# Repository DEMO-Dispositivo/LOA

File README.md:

# LOA
Robots for Lucifer's Ensemble LOA project.
Playing 3 drums made using Lavacolhos techniques inspired by the Arada drums and other percussions.
The boards are Arduino-based and can receive MIDI through DIN cable or play via SD Card.

## BOARDS

### Legba 
- Arduino MEGA
- 3 servos (5V)
- 7 solenoids (12V)
- 2 motors (5V or 12V)

### Damballah
- Arduino UNO
- 1 servo (5V)
- 3 solenoids (12V)
- 2 motors (5V or 12V)

### Samedi
- Arduino UNO
- 1 servo (5V)
- 3 solenoids (12V)
- 2 motors (5V or 12V)

## BOM
[BOM Spreadsheet](https://docs.google.com/spreadsheets/d/1H9ps_YcNi2U3gRdNnN2o0KlRJA077tAUcP5HMw0Rx48/edit?usp=sharing)

## SCHEMATICS
[Legba board](../master/schematics/Legba_schematic_rev1.pdf)

## MIDI Note Mapping
### Legba
- Note 0: solenoid 1
- Note 2: solenoid 2
- Note 4: solenoid 3
- Note 5: solenoid/motor 4
- Note 7: solenoid/motor 5
- Note/CC 9: servo 1
- Note 36: solenoid 6
- Note 38: solenoid 7 
- Note 40: solenoid 8
- Note/CC 43: servo 2
- Note/CC 45: servo 3

### Damballah
- Note 12: solenoid 1
- Note 14: solenoid 2
- Note 16: solenoid 3
- Note 17: solenoid/motor 4
- Note 19: solenoid/motor 5
- Note 21: servo 1

### Samedi
- Note 24: solenoid 1
- Note 26: solenoid 2
- Note 28: solenoid 3
- Note 29: solenoid/motor 4
- Note 31: solenoid/motor 5
- Note 33: servo 1

## Special thanks to
- Américo Simões
- Tiago Fróis
- Gil MAC and Cláudio Vidal
- FEUP (Faculty of Engineering - University of Porto)
- FCT (Foundation for Science and Technology)

[![CC BY-NC 4.0][cc-by-nc-shield]][cc-by-nc]

This work is licensed under a
[Creative Commons Attribution-NonCommercial 4.0 International License][cc-by-nc].

[![CC BY-NC 4.0][cc-by-nc-image]][cc-by-nc]

[cc-by-nc]: https://creativecommons.org/licenses/by-nc/4.0/
[cc-by-nc-image]: https://licensebuttons.net/l/by-nc/4.0/88x31.png
[cc-by-nc-shield]: https://img.shields.io/badge/License-CC%20BY--NC%204.0-lightgrey.svg

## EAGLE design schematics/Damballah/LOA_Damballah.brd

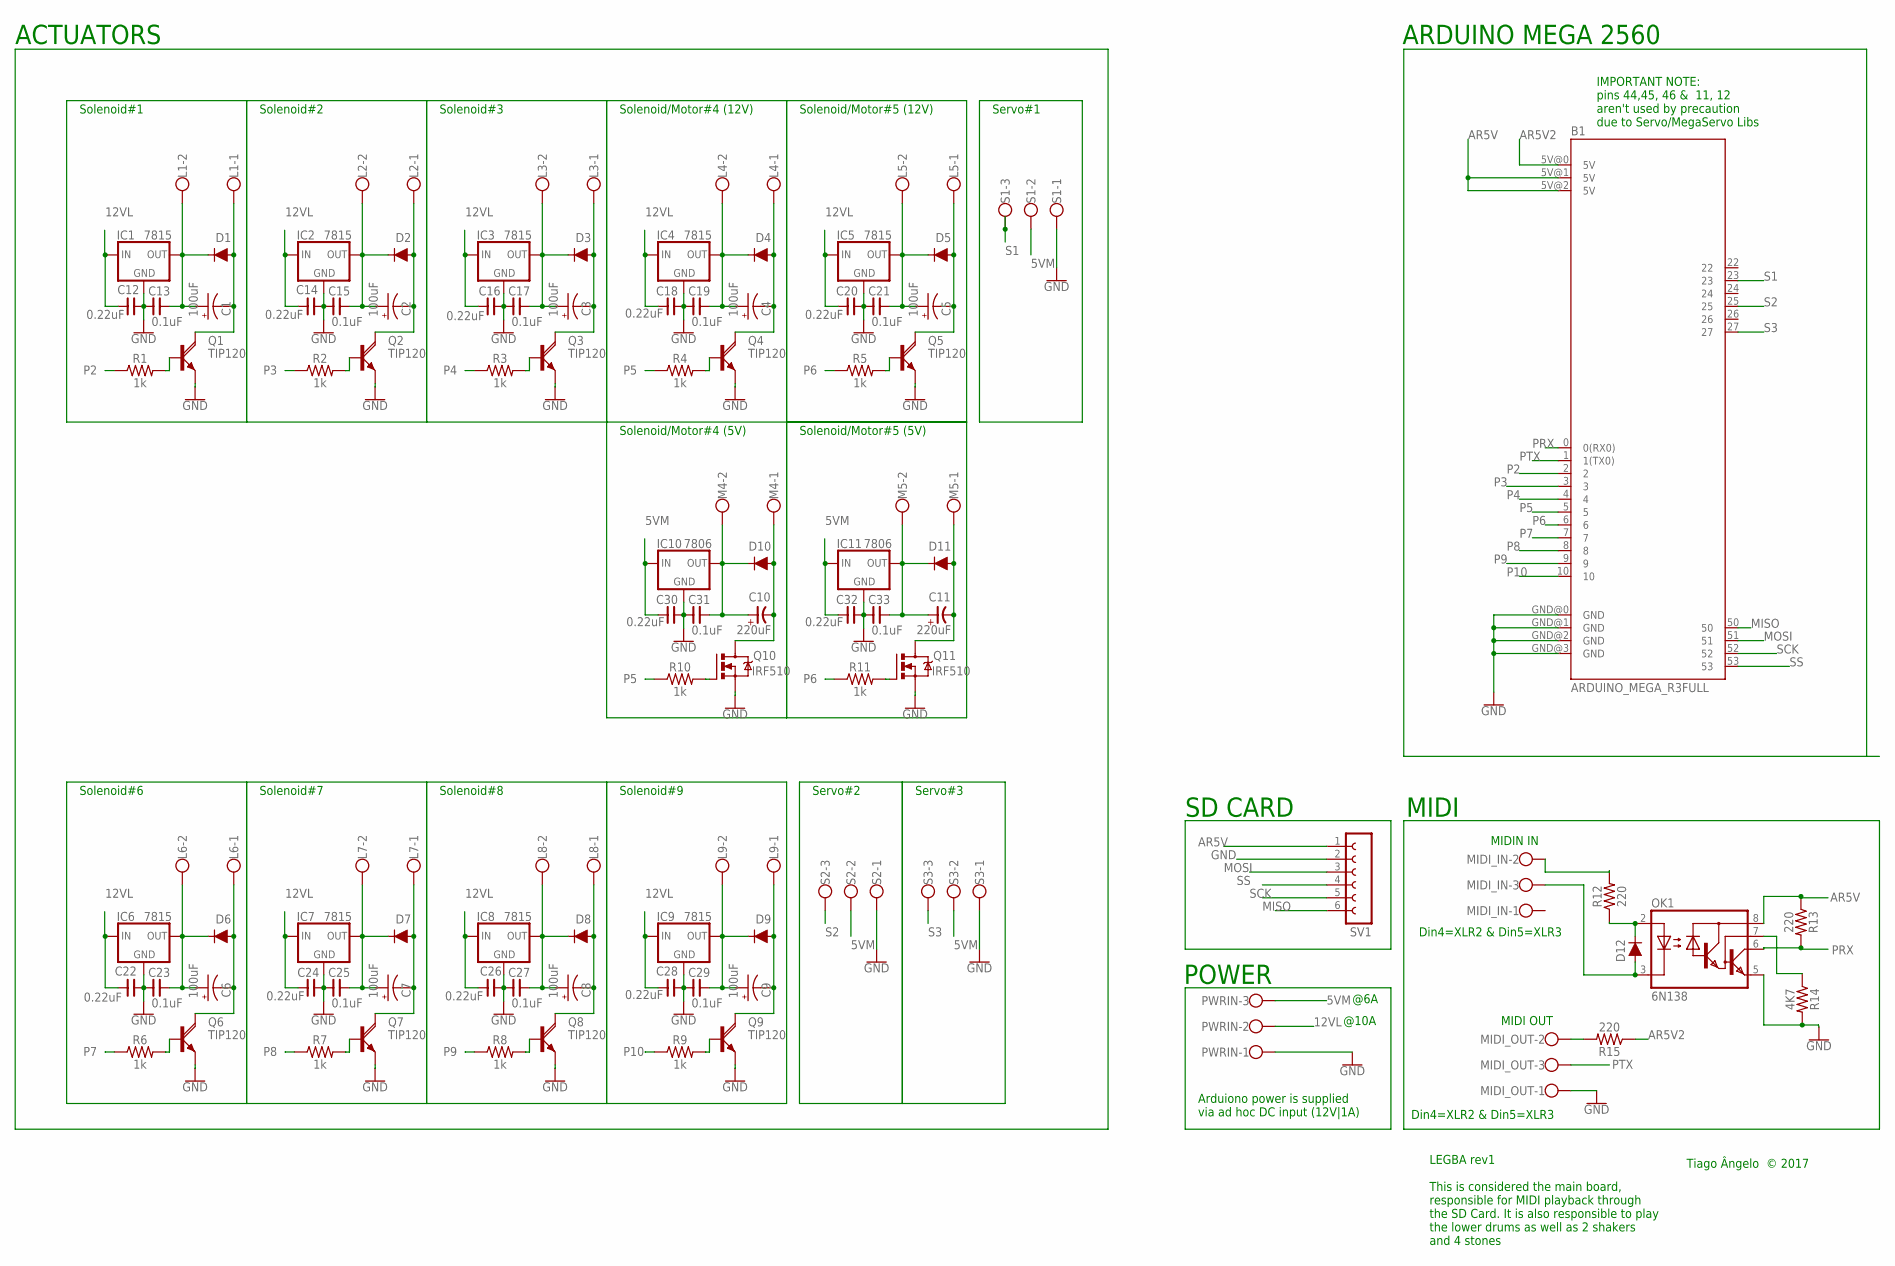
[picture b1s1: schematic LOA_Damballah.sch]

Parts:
B1: ARDUINO_MEGA_R3FULL; ARDUINO_MEGA
C1, C2, C3, C4, C5, C6, C7, C8, C9: 100uF; E3,5-8
C10, C11: 220uF; E-035X080
C12, C14, C16, C18, C20, C22, C24, C26, C28, C30, C32: 0.22uF; C025-050X025
C13, C15, C17, C19, C21, C23, C25, C27, C29, C31, C33: 0.1uF; C025-050X025
D1, D2, D3, D4, D5, D6, D7, D8, D9, D10, D11: 1A/50V/1.1V; DIODE-1N4001-KIT
D12: 200mA/100V/1V; DIODE-1N4148
IC1, IC2, IC3, IC4, IC5, IC6, IC7, IC8, IC9: 7815; 78XXS
IC10, IC11: 7806; 78XXS
L1, L2, L3, L4, L5, L6, L7, L8, L9: W237-102
M4, M5: W237-102
MIDI_IN: W237-103
MIDI_OUT: W237-103
OK1: 6N138; DIL08
PWRIN: W237-103
Q1, Q2, Q3, Q4, Q5, Q6, Q7, Q8, Q9: TIP120; ROCKETFARM_TO220AV
Q10, Q11: IRF510; TO220BV
R1, R2, R3, R4, R5, R6, R7, R8, R9, R10, R11: 1k; AXIAL-0.1
R12, R13, R15: 220; AXIAL-0.3
R14: 4K7; AXIAL-0.3
S1, S2, S3: W237-103
SV1: FE06W

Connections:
5VM: C30.1, C32.1, IC10.IN, IC11.IN, PWRIN.3, S1.2, S2.2, S3.2
12VL: C12.1, C14.1, C16.1, C18.1, C20.1, C22.1, C24.1, C26.1, C28.1, IC1.IN, IC2.IN, IC3.IN, IC4.IN, IC5.IN, IC6.IN, IC7.IN, IC8.IN, IC9.IN, PWRIN.2
AR5V: B1.5V@1 (5V), B1.5V@2 (5V), OK1.8 (VCC), R13.P$1 (1), SV1.1
AR5V2: B1.5V@0 (5V), R15.P$1 (1)
GND: B1.GND@0 (GND), B1.GND@1 (GND), B1.GND@2 (GND), B1.GND@3 (GND), C12.2, C13.1, C14.2, C15.1, C16.2, C17.1, C18.2, C19.1, C20.2, C21.1, C22.2, C23.1, C24.2, C25.1, C26.2, C27.1, C28.2, C29.1, C30.2, C31.1, C32.2, C33.1, IC1.GND, IC2.GND, IC3.GND, IC4.GND, IC5.GND, IC6.GND, IC7.GND, IC8.GND, IC9.GND, IC10.GND, IC11.GND, MIDI_OUT.1, OK1.5 (GND), PWRIN.1, Q1.E, Q2.E, Q3.E, Q4.E, Q5.E, Q6.E, Q7.E, Q8.E, Q9.E, Q10.S, Q11.S, R14.P$2 (2), S1.1, S2.1, S3.1, SV1.2
L1-1: C1.-, D1.A, L1.1, Q1.C
L1-2: C1.+, C13.2, D1.C, IC1.OUT, L1.2
L2-1: C2.-, D2.A, L2.1, Q2.C
L2-2: C2.+, C15.2, D2.C, IC2.OUT, L2.2
L3-1: C3.-, D3.A, L3.1, Q3.C
L3-2: C3.+, C17.2, D3.C, IC3.OUT, L3.2
L4-1: C4.-, D4.A, L4.1, Q4.C
L4-2: C4.+, C19.2, D4.C, IC4.OUT, L4.2
L5-1: C5.-, D5.A, L5.1, Q5.C
L5-2: C5.+, C21.2, D5.C, IC5.OUT, L5.2
L6-1: C6.-, D6.A, L6.1, Q6.C
L6-2: C6.+, C23.2, D6.C, IC6.OUT, L6.2
L7-1: C7.-, D7.A, L7.1, Q7.C
L7-2: C7.+, C25.2, D7.C, IC7.OUT, L7.2
L8-1: C8.-, D8.A, L8.1, Q8.C
L8-2: C8.+, C27.2, D8.C, IC8.OUT, L8.2
L9-1: C9.-, D9.A, L9.1, Q9.C
L9-2: C9.+, C29.2, D9.C, IC9.OUT, L9.2
M4-1: C10.-, D10.A, M4.1, Q10.D
M4-2: C10.+, C31.2, D10.C, IC10.OUT, M4.2
M5-1: C11.-, D11.A, M5.1, Q11.D
M5-2: C11.+, C33.2, D11.C, IC11.OUT, M5.2
MISO: B1.50, SV1.6
MOSI: B1.51, SV1.3
unnamed: Q10.G, R10.P$2 (2)
unnamed: MIDI_OUT.2, R15.P$2 (2)
unnamed: Q2.B, R2.P$2 (2)
unnamed: Q3.B, R3.P$2 (2)
unnamed: Q4.B, R4.P$2 (2)
unnamed: Q5.B, R5.P$2 (2)
unnamed: Q11.G, R11.P$2 (2)
unnamed: Q6.B, R6.P$2 (2)
unnamed: Q7.B, R7.P$2 (2)
unnamed: Q8.B, R8.P$2 (2)
unnamed: Q1.B, R1.P$2 (2)
unnamed: Q9.B, R9.P$2 (2)
unnamed: D12.A, MIDI_IN.3, OK1.3 (C)
unnamed: D12.C, OK1.2 (A), R12.P$1 (1)
unnamed: MIDI_IN.2, R12.P$2 (2)
unnamed: OK1.7 (VB), R14.P$1 (1)
P2: B1.2, R1.P$1 (1)
P3: B1.3, R2.P$1 (1)
P4: B1.4, R3.P$1 (1)
P5: B1.5, R4.P$1 (1), R10.P$1 (1)
P6: B1.6, R5.P$1 (1), R11.P$1 (1)
P7: B1.7, R6.P$1 (1)
P8: B1.8, R7.P$1 (1)
P9: B1.9, R8.P$1 (1)
P10: B1.10, R9.P$1 (1)
PRX: B1.0 (0(RX0)), OK1.6 (VO), R13.P$2 (2)
PTX: B1.1 (1(TX0)), MIDI_OUT.3
S1: B1.23, S1.3
S2: B1.25, S2.3
S3: B1.27, S3.3
SCK: B1.52, SV1.5
SS: B1.53, SV1.4

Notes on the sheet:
Tiago Ângelo © 2017
Din4=XLR2 & Din5=XLR3
MIDI OUT
MIDIN IN
MIDI
POWER
Arduiono power is supplied via ad hoc DC input (12V|1A)
IMPORTANT NOTE: pins 44,45, 46 & 11, 12 aren't used by precaution due to Servo/MegaServo Libs
Solenoid#1
Solenoid#2
Solenoid#3
Servo#1
Solenoid/Motor#4 (5V)
Solenoid/Motor#5 (5V)
Solenoid/Motor#4 (12V)
Solenoid/Motor#5 (12V)
Servo#2
Servo#3
Solenoid#6
Solenoid#7
Solenoid#8
Solenoid#9
SD CARD
ARDUINO MEGA 2560
ACTUATORS
@10A
@6A
LEGBA rev1 This is considered the main board, responsible for MIDI playback through the SD Card. It is also responsible to play the lower drums as well as 2 shakers and 4 stones

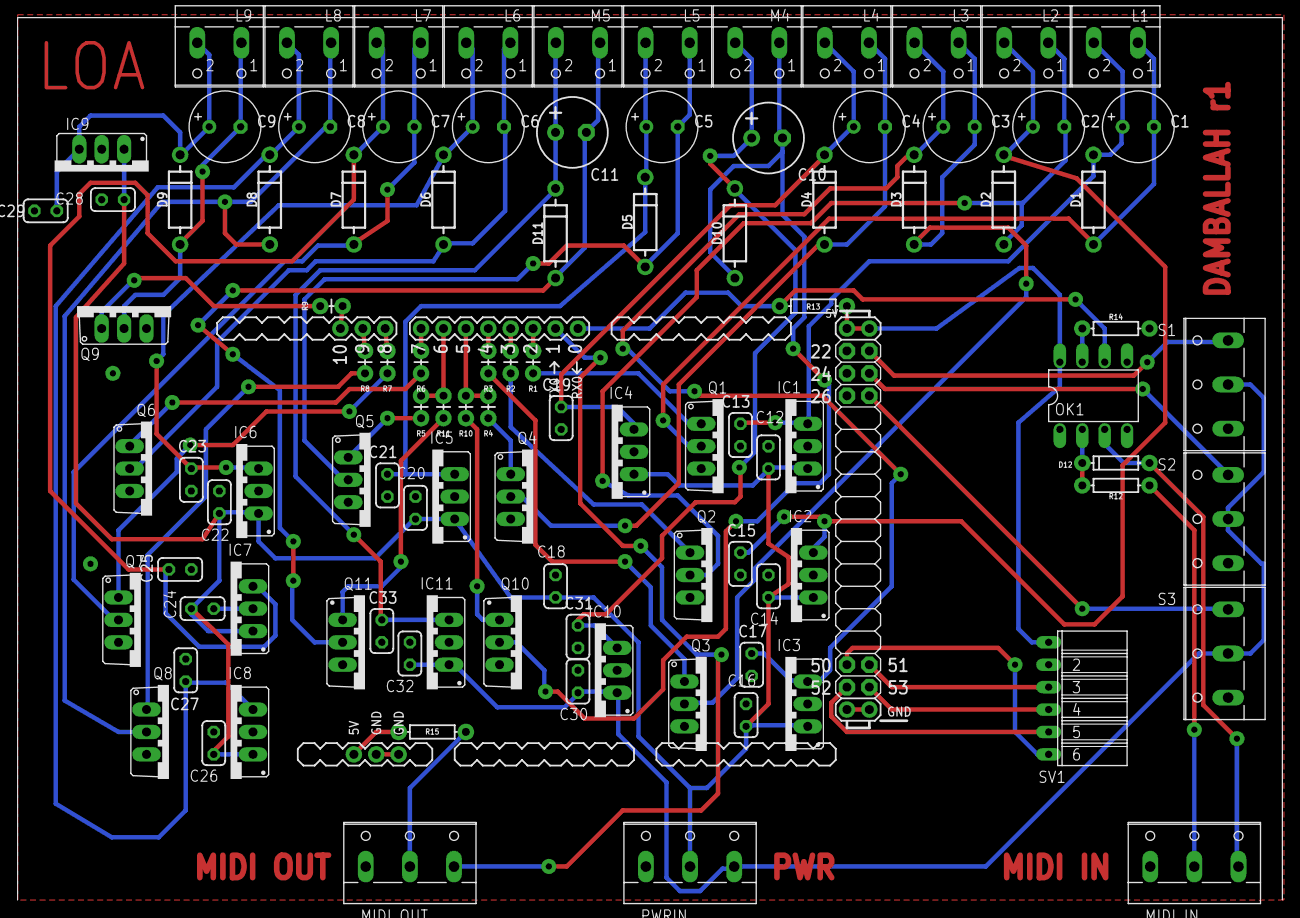
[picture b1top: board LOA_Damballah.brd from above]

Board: 2 copper layers, 143.3 x 100.0 mm, 102 parts (0 on the bottom side), 61 nets.

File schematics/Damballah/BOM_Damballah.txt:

Partlist exported from C:/Users/tiago/Documents/GitHub/LOA/schematics/Damballah/LOA_Damballah.sch at 25-09-2018 17:31

Qty Value               Device              Package            Parts                                                 Description                          
1                       FE06W               FE06W              SV1                                                   FEMALE HEADER                        
11                      W237-102            W237-102           L1, L2, L3, L4, L5, L6, L7, L8, L9, M4, M5            WAGO SCREW CLAMP                     
6                       W237-103            W237-103           MIDI_IN, MIDI_OUT, PWRIN, S1, S2, S3                  WAGO SCREW CLAMP                     
11  0.1uF               CNP-C025-050X025    C025-050X025       C13, C15, C17, C19, C21, C23, C25, C27, C29, C31, C33 NON-POLARIZED CAP                    
11  0.22uF              CNP-C025-050X025    C025-050X025       C12, C14, C16, C18, C20, C22, C24, C26, C28, C30, C32 NON-POLARIZED CAP                    
9   100uF               CPOL-USE3.5-8       E3,5-8             C1, C2, C3, C4, C5, C6, C7, C8, C9                    POLARIZED CAPACITOR, American symbol 
11  1A/50V/1.1V         DIODE-KIT2          DIODE-1N4001-KIT   D1, D2, D3, D4, D5, D6, D7, D8, D9, D10, D11          Diode                                
11  1k                  1KOHM-VERT-1/4W-1%  AXIAL-0.1          R1, R2, R3, R4, R5, R6, R7, R8, R9, R10, R11          1kO resistor                         
1   200mA/100V/1V       DIODE-1N4148        DIODE-1N4148       D12                                                   Diode                                
3   220                 1KOHM-HORIZ-1/4W-5% AXIAL-0.3          R12, R13, R15                                         1kO resistor                         
2   220uF               CP-E-035X080        E-035X080          C10, C11                                              POLARIZED CAP                        
1   4K7                 1KOHM-HORIZ-1/4W-5% AXIAL-0.3          R14                                                   1kO resistor                         
1   6N138               6N138               DIL08              OK1                                                   MOTOROLA OPTO COUPLER                
2   7806                78XXS               78XXS              IC10, IC11                                            VOLTAGE REGULATOR                    
9   7815                78XXS               78XXS              IC1, IC2, IC3, IC4, IC5, IC6, IC7, IC8, IC9           VOLTAGE REGULATOR                    
1   ARDUINO_MEGA_R3FULL ARDUINO_MEGA_R3FULL ARDUINO_MEGA       B1                                                    Arduino Mega R3                      
2   IRF510              IRF520              TO220BV            Q10, Q11                                              HEXFET Power MOSFET                  
9   TIP120              ROCKETFARM_TIP120V  ROCKETFARM_TO220AV Q1, Q2, Q3, Q4, Q5, Q6, Q7, Q8, Q9                    NPN DARLINGTON TRANSISTOR

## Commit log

2018-02-22 added BOM
2018-02-22 added gitignore
    ignore DS_Store and all folders starting with underscore "_"
2018-02-22 added schematic for Legba board
2018-02-22 link fix
2018-02-22 link fix2
2018-02-22 updated REAME
    added note mapping
2018-04-30 added schematics for Legba board
2018-04-30 updated gitignore
2018-04-30 Revert "updated gitignore"
    This reverts commit b36a427993d17d8ea599402f3e046fd2a2d82e0d.
2018-04-30 updated gitinore
2018-04-30 added 1st firmware sketch
    (copied from Phobos board #7)
2018-04-30 corrected MIDI library version
2018-05-16 updated gitignore
    due to folder name changes
2018-05-16 latest version
    working version
    needs verification
2018-05-28 Added Damballah firmware
2018-05-28 Added Samedi firmware
2018-05-28 updated servo controller
    added control for damballah and samedi
2018-09-08 uploaded etch files
2018-09-08 Uploaded samedi board
    Samedi and Damballah are prepared to handle 24V solenoids
    (the only difference in the etch to Legba is the 100uF caps)
2018-09-08 minor change
2018-09-08 uploaded Damballah board
2018-09-21 added mechanical components
2018-09-21 added report paper (PT)
2018-09-23 preliminary code
2018-09-25 preliminary tests
2018-09-25 uploaded BOM's
2018-10-25 added MIDI transcriptions
2018-10-25 cleanup
2018-10-25 patch to test robot
2018-10-25 patch to convert MIDI text files to RADA sequencer lists
2018-10-25 RADA version 1
2018-10-25 Revert "RADA version 1"
    This reverts commit 6184a96b92237c1f5dd021ca200d30d5047b9d39.
2018-10-25 RADA version 1
    First (working) version for installation at Festival Semibreve, Braga, 2018.
    This has a simpler version of the genetic algorithm to generate musical patterns
2025-08-14 Update LICENSE

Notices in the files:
parts and their libraries:
SparkFun-DiscreteSemi: Licensing: Creative Commons ShareAlike 4.0 International - https://creativecommons.org/licenses/by-sa/4.0
